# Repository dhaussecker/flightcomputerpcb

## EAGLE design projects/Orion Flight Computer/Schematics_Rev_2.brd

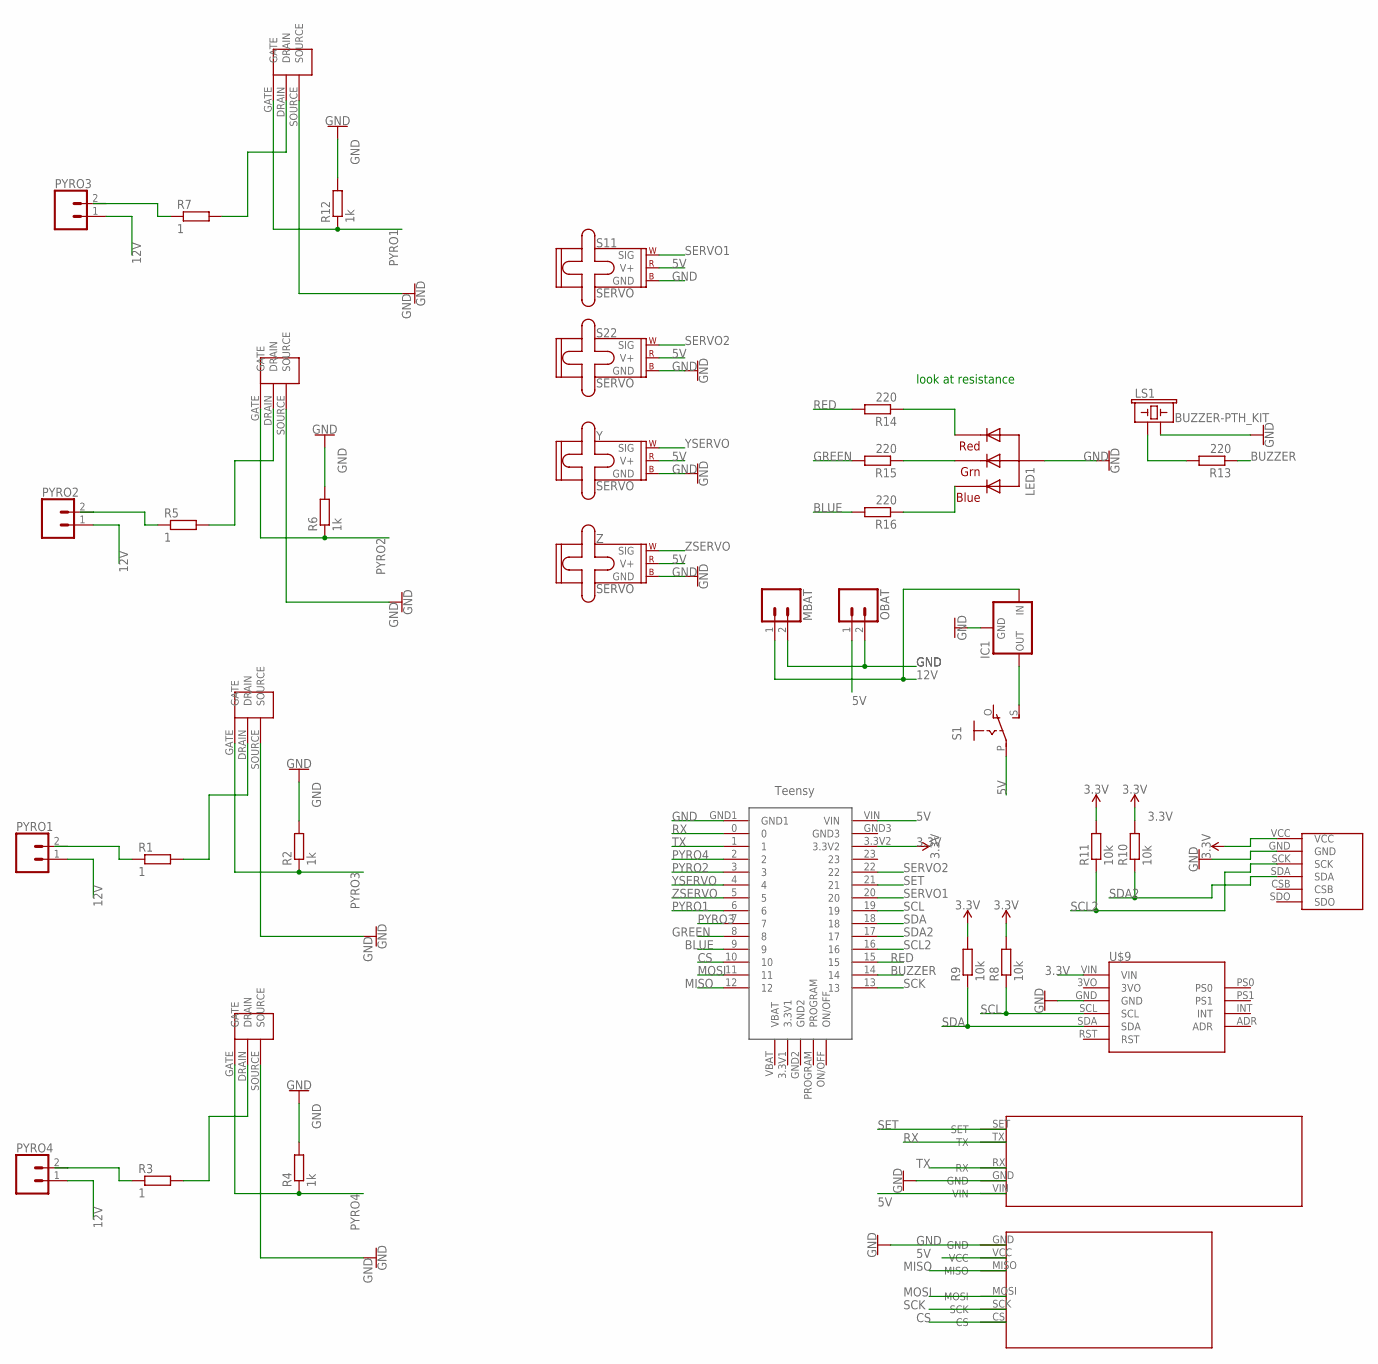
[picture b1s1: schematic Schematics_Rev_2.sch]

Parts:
IC1: 78XXS
LED1: RGBLED_CA-5MM; LED5MMRGB
LS1: BUZZER-PTH_KIT; BUZZER-12MM-KIT
MBAT: CONN_023.5MM; SCREWTERMINAL-3.5MM-2
OBAT: CONN_023.5MM; SCREWTERMINAL-3.5MM-2
PYRO1, PYRO2, PYRO3, PYRO4: CONN_023.5MM; SCREWTERMINAL-3.5MM-2
R1, R3, R5, R7: 1; 0204/7
R2, R4, R6, R12: 1k; 0204/7
R8, R9, R10, R11: 10k; 0204/7
R13, R14, R15, R16: 220; 0204/7
S1: EG1218S; EG1218
S11, S22: SERVO; 1X03
U$1: TEENSY-4.0
U$2: MICROSD
U$3: BMP280
U$4: HC-12
U$5, U$6, U$7, U$8: IRF520
U$9: BNO-055
Y: SERVO; 1X03
Z: SERVO; 1X03

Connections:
3.3V: R8.2, R9.2, R10.2, R11.2, U$1.3.3V2, U$3.VCC, U$9.VIN
5V: OBAT.1, S1.P, S11.2 (V+), S22.2 (V+), U$1.VIN, U$2.VCC, U$4.VIN, Y.2 (V+), Z.2 (V+)
12V: IC1.IN, MBAT.1, PYRO1.1, PYRO2.1, PYRO3.1, PYRO4.1
29: LS1.+ (1), R13.2
BLUE: R16.2, U$1.9
BUZZER: R13.1, U$1.14
CS: U$1.10, U$2.CS
GND: IC1.GND, LED1.2 (VCC), LS1.- (2), MBAT.2, OBAT.2, R2.2, R4.2, R6.2, R12.2, S11.3 (GND), S22.3 (GND), U$1.GND1, U$2.GND, U$3.GND, U$4.GND, U$5.SOURCE, U$6.SOURCE, U$7.SOURCE, U$8.SOURCE, U$9.GND, Y.3 (GND), Z.3 (GND)
GREEN: R15.2, U$1.8
MISO: U$1.12, U$2.MISO
MOSI: U$1.11, U$2.MOSI
unnamed: PYRO1.2, R1.1
unnamed: R1.2, U$6.DRAIN
unnamed: PYRO4.2, R3.1
unnamed: R3.2, U$5.DRAIN
unnamed: PYRO2.2, R5.1
unnamed: R5.2, U$7.DRAIN
unnamed: PYRO3.2, R7.1
unnamed: R7.2, U$8.DRAIN
unnamed: LED1.1 (RED), R14.1
unnamed: LED1.3 (GREEN), R15.1
unnamed: IC1.OUT, S1.S
unnamed: LED1.4 (BLUE), R16.1
PYRO1: R12.1, U$1.6, U$8.GATE
PYRO2: R6.1, U$1.3, U$7.GATE
PYRO3: R2.1, U$1.7, U$6.GATE
PYRO4: R4.1, U$1.2, U$5.GATE
RED: R14.2, U$1.15
RX: U$1.0, U$4.TX
SCK: U$1.13, U$2.SCK
SCL: R8.1, U$1.19, U$9.SCL
SCL2: R11.1, U$1.16, U$3.SCK
SDA: R9.1, U$1.18, U$9.SDA
SDA2: R10.1, U$1.17, U$3.SDA
SERVO1: S11.1 (SIG), U$1.20
SERVO2: S22.1 (SIG), U$1.22
SET: U$1.21, U$4.SET
TX: U$1.1, U$4.RX
YSERVO: U$1.4, Y.1 (SIG)
ZSERVO: U$1.5, Z.1 (SIG)

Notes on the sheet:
look at resistance

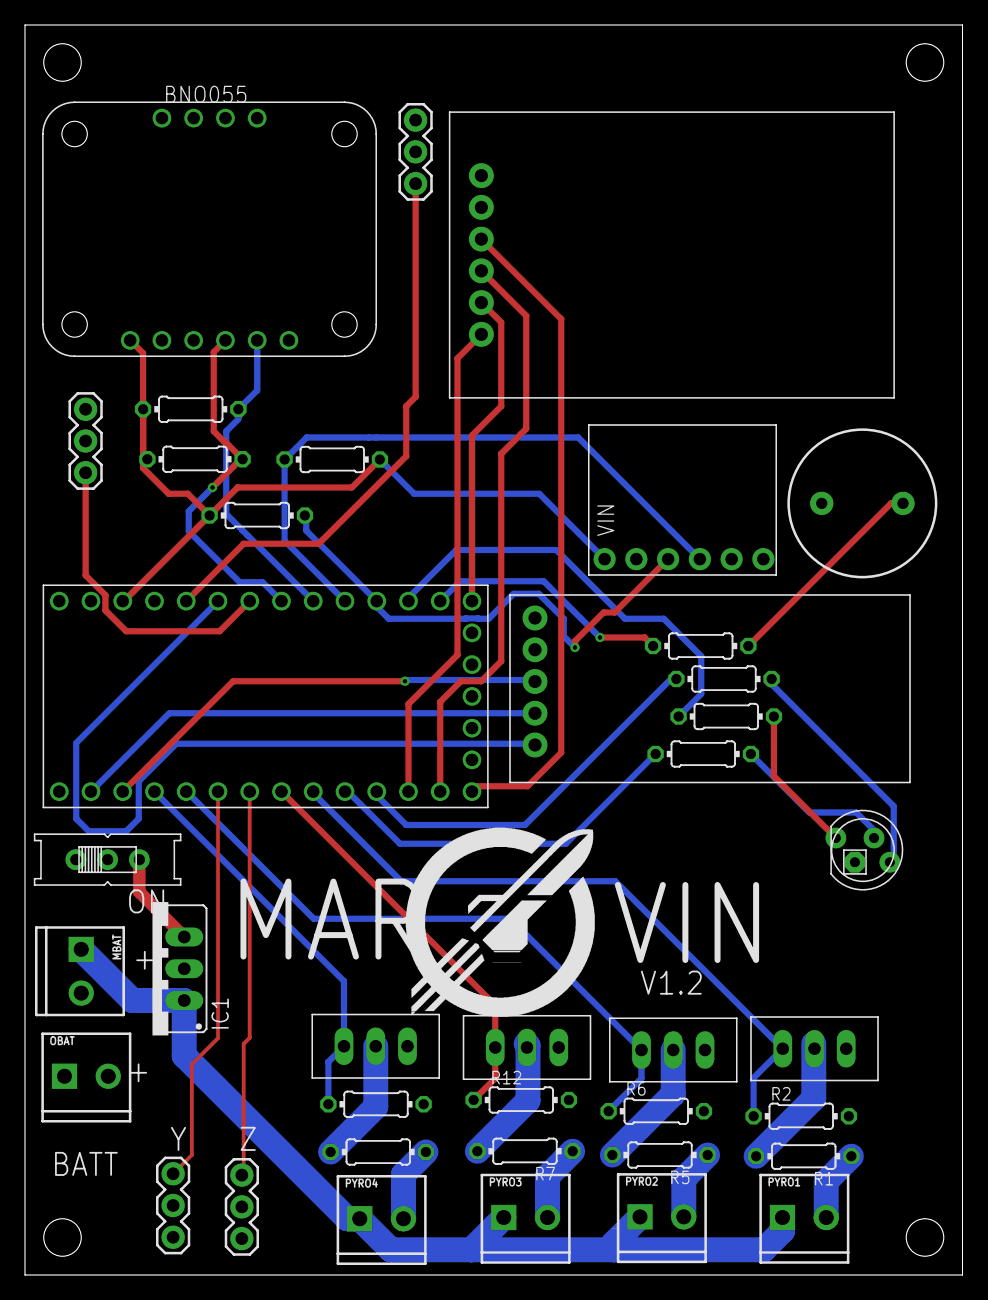
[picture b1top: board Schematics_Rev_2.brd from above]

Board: 2 copper layers, 75.0 x 100.0 mm, 39 parts (0 on the bottom side), 40 nets.

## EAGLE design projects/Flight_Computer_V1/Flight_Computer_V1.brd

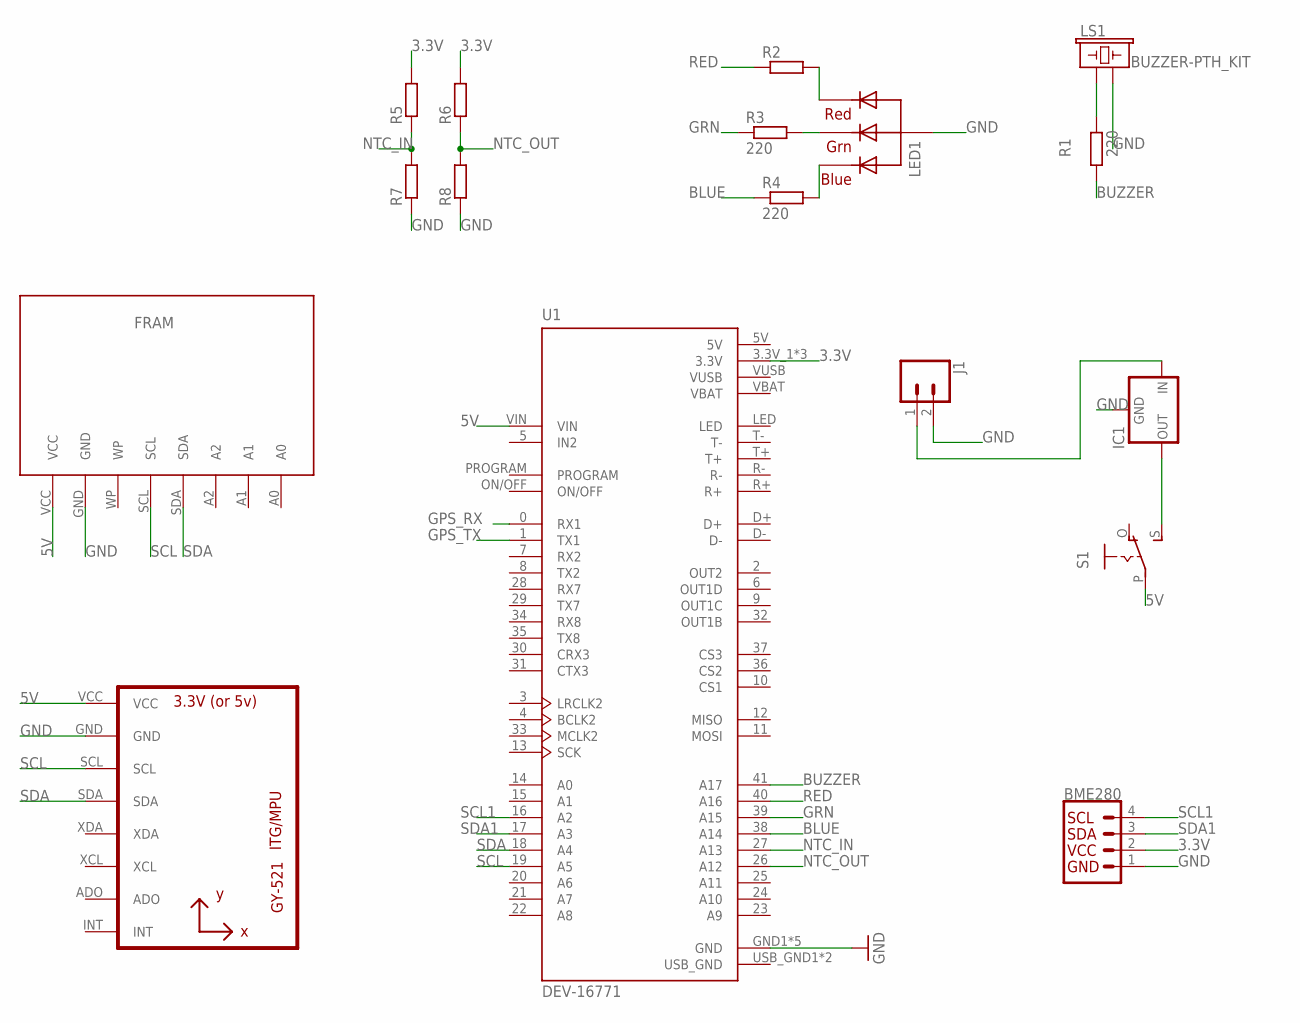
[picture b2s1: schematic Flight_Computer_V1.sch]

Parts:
BME280: I2C_STANDARD; 1X04
FRAM: FRAM_I2C
IC1: 78XXS
J1: CONN_023.5MM; SCREWTERMINAL-3.5MM-2
LED1: RGBLED_CA-5MM; LED5MMRGB
LS1: BUZZER-PTH_KIT; BUZZER-12MM-KIT
R1, R3, R4: 220; 0204/7
R2, R5, R6, R7, R8: R-EU_0204/7; 0204/7
S1: EG1218S; EG1218
U1: DEV-16771; MODULE_DEV-16771
U2: GY-521MPU6050; GY-521

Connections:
3.3V: BME280.2, R5.2, R6.2, U1.3.3V_1 (3.3V), U1.3.3V_2 (3.3V), U1.3.3V_3 (3.3V)
5V: FRAM.VCC, S1.P, U1.5V, U1.VIN, U2.VCC
BLUE: R4.1, U1.38 (A14)
BUZZER: R1.1, U1.41 (A17)
GND: BME280.1, FRAM.GND, IC1.GND, J1.2, LED1.2 (VCC), LS1.- (2), R7.1, R8.1, U1.GND1 (GND), U1.GND2 (GND), U1.GND3 (GND), U1.GND4 (GND), U1.GND5 (GND), U2.GND
GPS_RX: U1.0 (RX1)
GPS_TX: U1.1 (TX1)
GRN: R3.1, U1.39 (A15)
unnamed: LS1.+ (1), R1.2
unnamed: LED1.1 (RED), R2.2
unnamed: LED1.3 (GREEN), R3.2
unnamed: LED1.4 (BLUE), R4.2
unnamed: IC1.IN, J1.1
unnamed: IC1.OUT, S1.S
NTC_IN: R5.1, R7.2, U1.27 (A13)
NTC_OUT: R6.1, R8.2, U1.26 (A12)
RED: R2.1, U1.40 (A16)
SCL: FRAM.SCL, U1.19 (A5), U2.SCL
SCL1: BME280.4, U1.16 (A2)
SDA: FRAM.SDA, U1.18 (A4), U2.SDA
SDA1: BME280.3, U1.17 (A3)
USB_GND: U1.USB_GND1 (USB_GND), U1.USB_GND2 (USB_GND)

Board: 2 copper layers, 17 parts (0 on the bottom side), 20 nets, no tracks yet.

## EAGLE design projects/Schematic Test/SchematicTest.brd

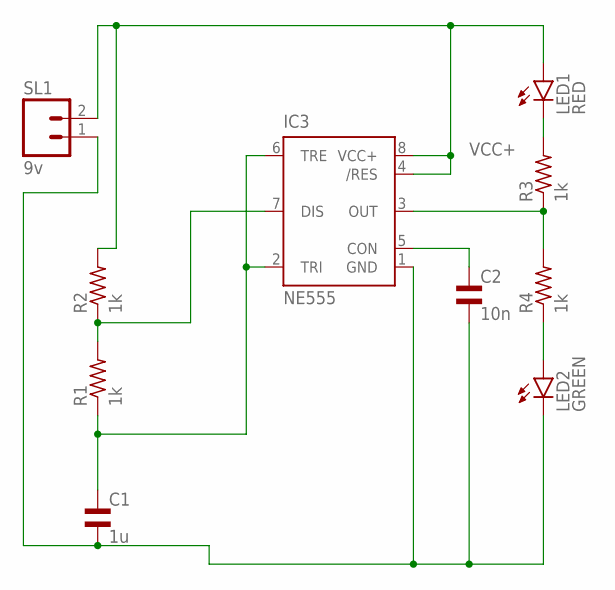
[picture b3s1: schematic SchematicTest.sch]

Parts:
C1: 1u; EU25-10
C2: 10n; EU25-10
IC3: NE555; DIL-08
LED1: RED; LED5MM
LED2: GREEN; LED5MM
R1, R2, R3, R4: 1k; 0204V
SL1: 9v; 02P

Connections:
GND: C1.2, C2.2, IC3.1 (GND), LED2.K (C), SL1.1
unnamed: IC3.3 (OUT), R3.1, R4.2
unnamed: LED2.A, R4.1
unnamed: LED1.K (C), R3.2
unnamed: IC3.7 (DIS), R1.2, R2.1
unnamed: C1.1, IC3.2 (TRI), IC3.6 (TRE), R1.1
unnamed: C2.1, IC3.5 (CON)
VCC+: IC3.4 (/RES), IC3.8 (VCC+), LED1.A, R2.2, SL1.2

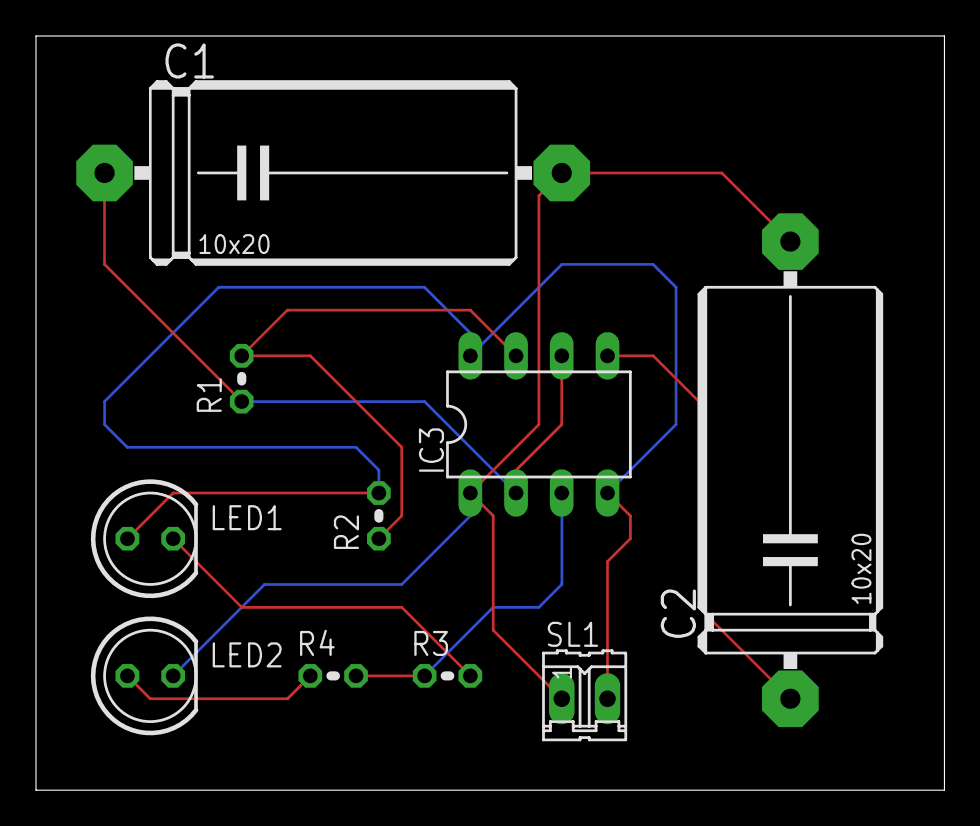
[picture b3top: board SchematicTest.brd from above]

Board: 2 copper layers, 50.5 x 41.9 mm, 10 parts (0 on the bottom side), 8 nets.

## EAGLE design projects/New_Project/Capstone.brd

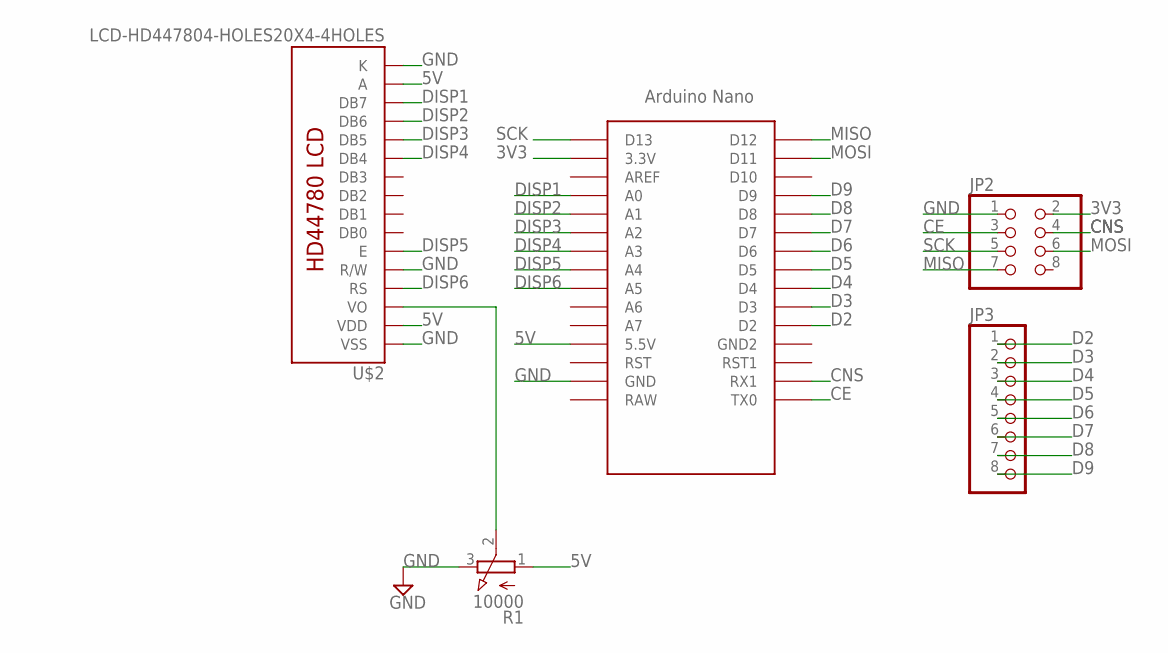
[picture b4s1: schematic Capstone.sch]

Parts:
JP2: PINHD-2X4; 2X04
JP3: PINHD-1X8; 1X08
R1: 10000; 3RP/1610N
U$1: NANO
U$2: LCD-HD447804-HOLES20X4-4HOLES; LCD-20X4-4HOLES

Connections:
3V3: JP2.2, U$1.3.3V
5V: R1.1 (A), U$1.5V (5.5V), U$2.P$2 (VDD), U$2.P$15 (A)
CE: JP2.3, U$1.TX0
CNS: JP2.4, U$1.RX1
D2: JP3.1, U$1.D2
D3: JP3.2, U$1.D3
D4: JP3.3, U$1.D4
D5: JP3.4, U$1.D5
D6: JP3.5, U$1.D6
D7: JP3.6, U$1.D7
D8: JP3.7, U$1.D8
D9: JP3.8, U$1.D9
DISP1: U$1.A0, U$2.P$14 (DB7)
DISP2: U$1.A1, U$2.P$13 (DB6)
DISP3: U$1.A2, U$2.P$12 (DB5)
DISP4: U$1.A3, U$2.P$11 (DB4)
DISP5: U$1.A4, U$2.P$6 (E)
DISP6: U$1.A5, U$2.P$4 (RS)
DISP8: R1.2 (S), U$2.P$3 (VO)
GND: JP2.1, R1.3 (E), U$1.GND, U$2.P$1 (VSS), U$2.P$5 (R/W), U$2.P$16 (K)
MISO: JP2.7, U$1.D12
MOSI: JP2.6, U$1.D11
SCK: JP2.5, U$1.D13

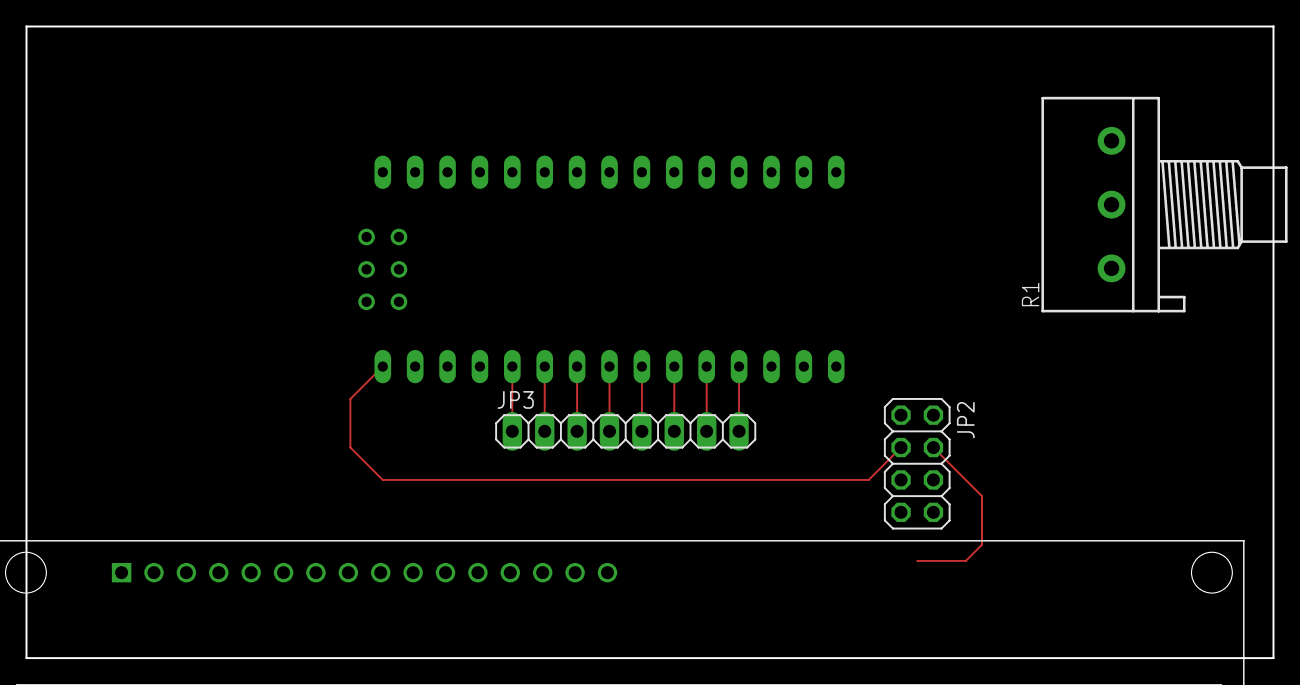
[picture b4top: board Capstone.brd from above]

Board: 2 copper layers, 97.8 x 49.5 mm, 5 parts (0 on the bottom side), 23 nets.

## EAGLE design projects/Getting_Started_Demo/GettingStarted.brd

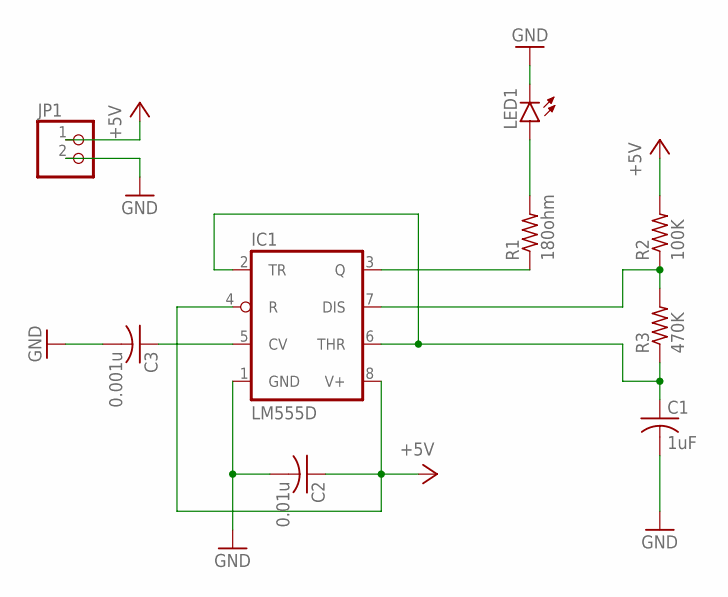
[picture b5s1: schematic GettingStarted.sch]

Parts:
C1: 1uF; C0805
C2: 0.01u; C0805
C3: 0.001u; C0805
IC1: LM555D; SO08
JP1: PINHD-1X2; 1X02
LED1: LED5MM
R1: 180ohm; R0805
R2: 100K; R0805
R3: 470K; R0805

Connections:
+5V: C2.1, IC1.4 (R), IC1.8 (V+), JP1.1, R2.2
GND: C1.2, C2.2, C3.2, IC1.1 (GND), JP1.2, LED1.K (C)
unnamed: IC1.3 (Q), R1.1
unnamed: IC1.7 (DIS), R2.1, R3.2
unnamed: C1.1, IC1.2 (TR), IC1.6 (THR), R3.1
unnamed: C3.1, IC1.5 (CV)
unnamed: LED1.A, R1.2

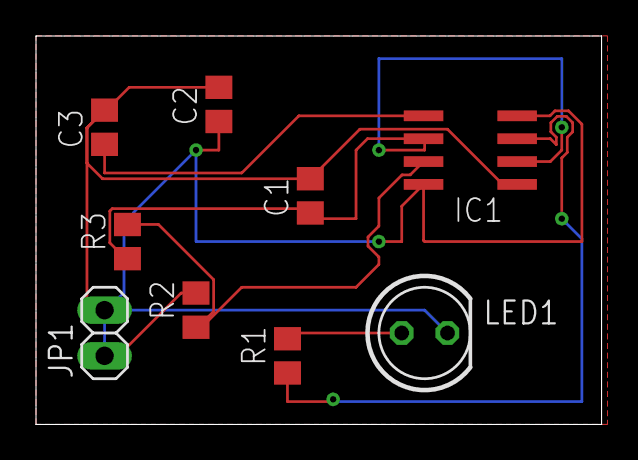
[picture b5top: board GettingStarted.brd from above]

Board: 2 copper layers, 31.4 x 21.6 mm, 9 parts (0 on the bottom side), 7 nets.

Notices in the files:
parts and their libraries:
SparkFun-Electromechanical: Licensing: Creative Commons ShareAlike 4.0 International - https://creativecommons.org/licenses/by-sa/4.0
